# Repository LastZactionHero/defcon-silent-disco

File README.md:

# DEF CON Silent Disco Badge

A wearable silent disco. Every badge plays DJ mixes from its own memory
card to your headphones, runs a light show that matches the music, and can
**sync to a friend's badge over infrared** — same song, same moment, lights
flashing together.

## How to use it

1. Flip the **power switch**. Plug **headphones** into the top jack.
2. It starts playing where it last left off.

| Button | Does |
|---|---|
| **CHANNEL** | Next channel. Each channel is one DJ mix that loops forever. |
| **VOL + / −** | Volume, 8 steps. Hold to ramp. Bottom step is mute. |
| **SYNC** | Join a friend — see below. |
| **CHANNEL, held 10 s** | Reset the badge. |

**Syncing:** press SYNC — your music pauses and the badge listens for up to
~25 seconds. Touch your badge's jagged edge into your friend's (they
interlock — that's what the teeth are for) and it will pick up their
broadcast, jump to **their channel at their exact spot**, and both badges
shimmer to confirm. Every badge announces itself over IR every ~10 seconds,
so there's nothing to press on the other badge.

**The light show** is picked by the music: each track gets its own color
theme and animation, and every ~10 seconds the badge plays a short glitter
burst. Synced badges glitter at the same instant.

## If something's wrong

**Red blinking LEDs** are an error code — count which LEDs are lit
(leftmost = 1):

| Code | Meaning | Try |
|---|---|---|
| 1 | No SD card | Reseat the card, power cycle |
| 2 | Card is empty | Put MP3s on it (see below) |
| 3 | Card unreadable | Re-format / re-copy the card |
| 4 | Playback keeps failing | Power cycle; check the battery |

**Sounds distorted, buzzy, or "like a modem"? Swap the battery.** A dying
battery warps the audio and confuses the SD card before anything else —
it looks like a bug, and it never is.

## The SD card

Just MP3 files in the root of the card — nothing else needed:

```
/ElAndEu_Duis.mp3      ← channel 1
/InYourEyes.mp3        ← channel 2
/Sepultura.mp3         ← channel 3   (alphabetical order = channel order)
```

- Encode at **96 kbps CBR, 44.1 kHz stereo** — `firmware/tools/prepare_card.sh`
  does this for you (and matches loudness across mixes).
- The **filename chooses the light show** — rename a file, get new colors.
- A 128 MB card holds about **2 h 54 m** (~29 min × 6 channels).

## Coming soon

- **Plain MP3-player firmware** — reflash the badge as a normal
  pocket music player (next/prev/pause instead of channels + sync). The
  code exists in this repo; a one-step installer is TODO.
- A **phone app that joins the disco by camera** — the glitter bursts
  encode the channel and timecode, so a phone can watch any badge and
  start playing along. Groundwork is shipped; app is TODO.

## Flashing / updating the firmware

Everything a badge runs is in this repo — [`firmware/`](firmware/) —
including the prebuilt firmware image
[`firmware-mp3-universal.uf2`](firmware/firmware-mp3-universal.uf2)
(one image works on every badge in the run).

**The easy way** (macOS/Linux, needs Python 3 and
[`mpremote`](https://docs.micropython.org/en/latest/reference/mpremote.html)):

```sh
git clone https://github.com/LastZactionHero/defcon-silent-disco.git
cd defcon-silent-disco/firmware
tools/flash_badge.sh        # follow the prompts: plug in, wait for DONE
```

The script does the whole thing — flashes the UF2, installs the badge
software, verifies it, reboots into the disco.

**By hand:** hold **BOOTSEL** while plugging in USB → a drive called
`RPI-RP2` appears → copy the `.uf2` onto it → the badge reboots → then copy
the `.py` files from `firmware/` onto it with `mpremote`. (macOS quirk: use
the script or `dd` — a plain Finder/`cp` copy of a UF2 can silently fail.
The drive *disappearing* is how you know the flash worked.)

Full details, including rebuilding the firmware from source:
[`firmware/README.md`](firmware/README.md).

## Under the hood

RP2040 · MicroPython + native MP3 decoder · 4× addressable RGB LEDs ·
IR sync · sawtooth interlocking edges · USB-C. The full technical story —
firmware architecture, the test suite, build-your-own instructions, and
the bring-up war stories — lives in [`firmware/README.md`](firmware/README.md).
KiCad sources are in [`defcon_badge/`](defcon_badge/), fab files in
[`defcon_badge/fab_rev2.zip`](defcon_badge/fab_rev2.zip).

## Credits

Designed and built by [**Pikkolo Assembly**](https://pikkoloassembly.com/).
Demo mixes are Creative Commons (attribution in `CREDITS.txt` on each
card). MP3 decoding by the Helix decoder via
[picomp3lib](https://github.com/ikjordan/picomp3lib).

MIT licensed — see [LICENSE](LICENSE). Go make a dance floor.

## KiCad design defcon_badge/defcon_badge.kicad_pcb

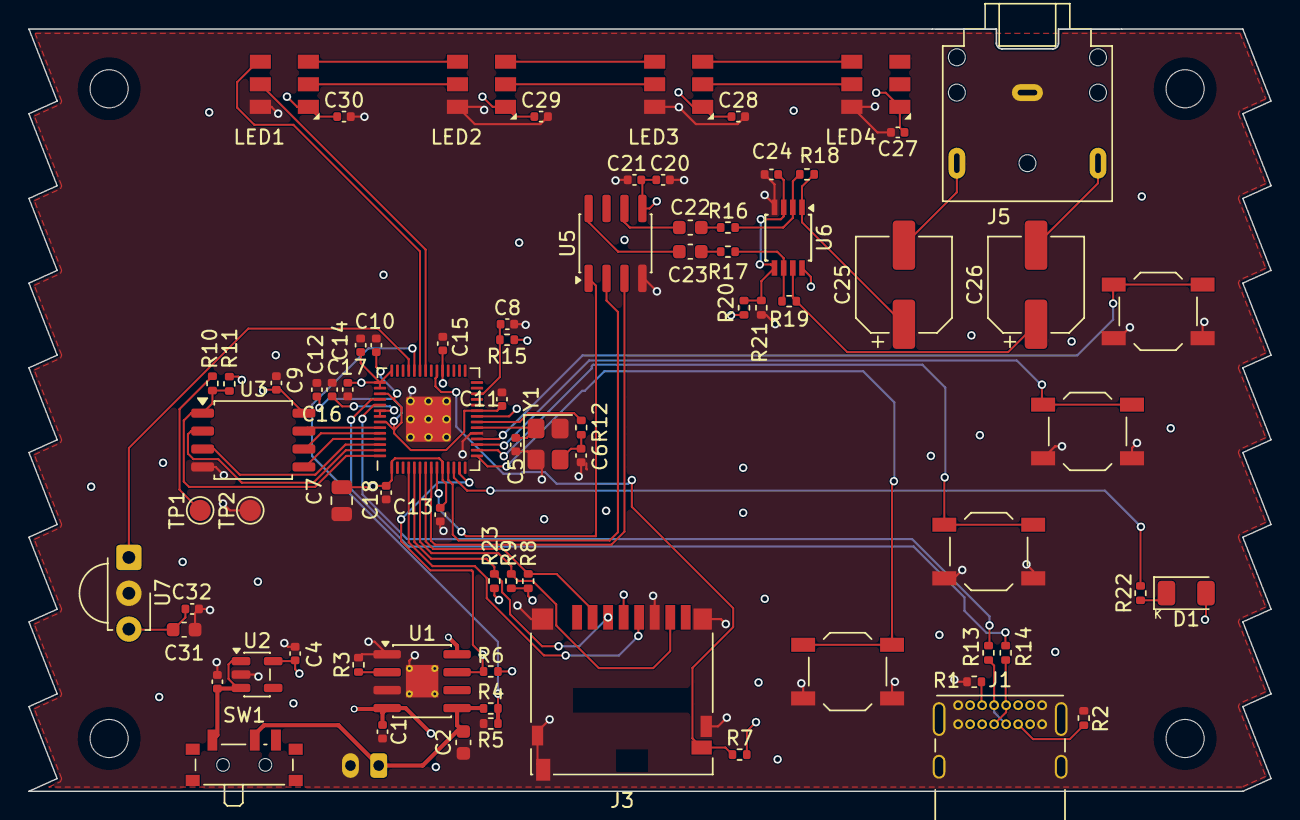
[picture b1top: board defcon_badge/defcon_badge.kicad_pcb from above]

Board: 4 copper layers, 88.0 x 54.0 mm, 82 parts (1 on the bottom side), 61 nets.

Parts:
C1, C3, C4, C12, C14: 1u; C_0402_1005Metric
C2, C22, C23, C31: 10u; C_0603_1608Metric
C5, C6: 15p; C_0402_1005Metric
C7: 1u; C_0805_2012Metric
C8: 100nF; C_0402_1005Metric
C9, C10, C11, C13, C15, C16, C17, C18, C20, C30: 100n; C_0402_1005Metric
C21, C24: 10u; C_0402_1005Metric
C25, C26: 220u; CP_Elec_6.3x5.4
C27, C28, C29, C32: 10n; C_0402_1005Metric
CHANNEL1: TS-1187A; SW_SPST_TL3342
D1: IR LED 940 nm; LED_IR_1206_3216Metric
H1, H2, H3, H4: MountingHole; MountingHole_2.7mm_M2.5
J1: USB_C_Receptacle_USB2.0_16P; USB_C_Receptacle_GCT_USB4085
J2: JST-PH 2P; JST_PH_S2B-PH-K_1x02_P2.00mm_Horizontal
J3: microSD; microSD_HC_Hirose_DM3D-SF
J5: SJ1-3523N; Jack_3.5mm_CUI_SJ1-3523N_Horizontal
LED1, LED2, LED3, LED4: SK9822; LED_SK9822_5050
R1, R2: 5.1k; R_0402_1005Metric
R3: 2.4k; R_0402_1005Metric
R4, R5, R6, R18, R19: 100k; R_0402_1005Metric
R7, R8, R9, R15, R20, R21, R23: 10k; R_0402_1005Metric
R10, R12: 1k; R_0402_1005Metric
R11: DNF; R_0402_1005Metric
R13, R14: 27; R_0402_1005Metric
R16, R17: 47k; R_0402_1005Metric
R22: 150; R_0402_1005Metric
SW1: SS-12D00; SW_SPDT_PCM12
SYNC1: TS-1187A; SW_SPST_TL3342
TP1: BOOTSEL; TestPoint_Pad_D1.5mm
TP2: GND; TestPoint_Pad_D1.5mm
U1: TP4056; HSOP-8-1EP_3.9x4.9mm_P1.27mm_EP2.3x2.3mm_ThermalVias
U2: ME6211C33M5G; SOT-23-5
U3: WM2606220057; SOIC-8_5.3x5.3mm_P1.27mm
U4: RP2040; RP2040-QFN-56
U5: TM8211; SOIC-8_3.9x4.9mm_P1.27mm
U6: TDA1308; TSSOP-8_3x3mm_P0.65mm
U7: TSOP4838; Vishay_MINICAST-3Pin
VOL+1: TS-1187A; SW_SPST_TL3342
VOL-1: TS-1187A; SW_SPST_TL3342
Y1: ABM8-272-T3; Crystal_SMD_3225-4Pin_3.2x2.5mm

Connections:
+1V1: C10.1, C11.1, C12.1, U4.23 (DVDD), U4.45 (VREG_VOUT), U4.50 (DVDD)
+3.3V: R8.1, R9.1, R23.1
+3V3: C4.1, C7.1, C9.1, C13.1, C14.1, C15.1, C16.1, C17.1, C18.1, C20.1, C21.1, C27.1, C28.1, C29.1, C30.1, C31.1, C32.1, D1.1 (K), J3.4 (VDD), LED1.4 (VDD), LED2.4 (VDD), LED3.4 (VDD), LED4.4 (VDD), R6.1, R7.2, R11.1, R15.1, R20.1, U2.5 (VOUT), U3.8 (VCC), U4.1 (IOVDD), U4.10 (IOVDD), U4.22 (IOVDD), U4.33 (IOVDD), U4.42 (IOVDD), U4.43 (ADC_AVDD), U4.44 (VREG_IN), U4.48 (USB_VDD), U4.49 (IOVDD), U5.5 (VDD), U6.8 (VCC), U7.3 (VS)
/Audio/AMP_IN1-: R16.2, R18.1, U6.2 (IN1-)
/Audio/AMP_IN2-: R17.2, R19.1, U6.6 (IN2-)
/Audio/AMP_INL: C22.2, R16.1
/Audio/AMP_INR: C23.2, R17.1
/Audio/AMP_OUTL: C25.1, R18.2, U6.1 (OUT1)
/Audio/AMP_OUTR: C26.1, R19.2, U6.7 (OUT2)
/Audio/DAC_OUTL: C22.1, U5.6 (LCH)
/Audio/DAC_OUTR: C23.1, U5.8 (RCH)
/Audio/I2S_BCK: U4.9 (GPIO7), U5.1 (BCK)
/Audio/I2S_DIN: U4.8 (GPIO6), U5.3 (DIN)
/Audio/I2S_LRCK: U4.11 (GPIO8), U5.2 (WS)
/Audio/JACK_L: C25.2, J5.T (TIP)
/Audio/JACK_R: C26.2, J5.R (RING)
/Audio/VGND: C24.1, R20.2, R21.1, U6.3 (IN1+), U6.5 (IN2+)
/IO/BTN_CH: CHANNEL1.1, U4.18 (GPIO15)
/IO/BTN_SYNC: SYNC1.1, U4.15 (GPIO12)
/IO/BTN_VOL_DN: U4.16 (GPIO13), VOL-1.1
/IO/BTN_VOL_UP: U4.17 (GPIO14), VOL+1.1
/IO/SD_CS: J3.2 (DAT3/CD), R8.2, U4.7 (GPIO5)
/IO/SD_MISO: J3.7 (DAT0), R9.2, U4.6 (GPIO4)
/IO/SD_MOSI: J3.3 (CMD), R23.2, U4.5 (GPIO3)
/IO/SD_SCK: J3.5 (CLK), U4.4 (GPIO2)
/LEDs_IR/IR_DRIVE: D1.2 (A), R22.1
/LEDs_IR/IR_RX: U4.39 (GPIO27_ADC1), U7.1 (OUT)
/LEDs_IR/IR_TX: R22.2, U4.12 (GPIO9)
/LEDs_IR/LED_DAT: LED1.1 (DIN), U4.37 (GPIO25)
/LEDs_IR/LED_SCK: LED1.2 (CIN), U4.36 (GPIO24)
/MCU_Core/BOOTSEL: R10.2, TP1.1 (1_1)
/MCU_Core/QSPI_SCLK: U3.6 (CLK), U4.52 (QSPI_SCLK)
/MCU_Core/QSPI_SD0: U3.5 (DI(IO0)), U4.53 (QSPI_SD0)
/MCU_Core/QSPI_SD1: U3.2 (DO(IO1)), U4.55 (QSPI_SD1)
/MCU_Core/QSPI_SD2: U3.3 (IO2), U4.54 (QSPI_SD2)
/MCU_Core/QSPI_SD3: U3.7 (IO3), U4.51 (QSPI_SD3)
/MCU_Core/QSPI_SS: R10.1, R11.2, U3.1 (~CS), U4.56 (QSPI_SS)
/MCU_Core/RUN: C8.1, R15.2, U4.26 (RUN)
/MCU_Core/USB_DM: J1.A7 (D-), J1.B7 (D-), R14.1
/MCU_Core/USB_DP: J1.A6 (D+), J1.B6 (D+), R13.1
/MCU_Core/VBAT_SENSE: R4.2, R5.1, U4.38 (GPIO26_ADC0)
/MCU_Core/XIN: C5.1, U4.20 (XIN), Y1.1
/MCU_Core/XOUT: R12.1, U4.21 (XOUT)
/MCU_Core/~CHRG: R6.2, U1.7 (~CHRG), U4.13 (GPIO10)
/Power/BAT: C2.1, J2.2, R4.1, SW1.2 (B), U1.5 (BAT)
/Power/BAT_SW: C3.1, SW1.1 (A), U2.1 (VIN), U2.3 (EN)
/Power/CC1: J1.A5 (CC1), R1.1
/Power/CC2: J1.B5 (CC2), R2.1
/Power/PROG_SET: R3.1, U1.2 (PROG)
/Power/VBUS: C1.1, J1.A4 (VBUS), J1.A9 (VBUS), J1.B4 (VBUS), J1.B9 (VBUS), U1.4 (VCC), U1.8 (CE)
GND: C1.2, C2.2, C3.2, C4.2, C5.2, C6.2, C7.2, C8.2, C9.2, C10.2, C11.2, C12.2, C13.2, C14.2, C15.2, C16.2, C17.2, C18.2, C20.2, C21.2, C24.2, C27.2, C28.2, C29.2, C30.2, C31.2, C32.2, CHANNEL1.2, J1.A1 (GND), J1.A12 (GND), J1.B1 (GND), J1.B12 (GND), J1.SH (SHIELD), J2.1, J3.6 (VSS), J3.10 (DET_A), J3.SH (SHIELD), J5.S (SLEEVE), LED1.3 (GND), LED2.3 (GND), LED3.3 (GND), LED4.3 (GND), R1.2, R2.2, R3.2, R5.2, R21.2, SYNC1.2, TP2.1 (1_1), U1.1 (TEMP), U1.3 (GND), U1.9 (EP), U2.2 (GND), U3.4 (GND), U4.19 (TESTEN), U4.57 (GND), U5.4 (GND), U6.4 (VEE), U7.2 (GND), VOL+1.2, VOL-1.2, Y1.2, Y1.4
unnamed: C6.1, R12.2, Y1.3
unnamed: LED1.5 (COUT), LED2.2 (CIN)
unnamed: LED1.6 (DOUT), LED2.1 (DIN)
unnamed: LED2.5 (COUT), LED3.2 (CIN)
unnamed: LED2.6 (DOUT), LED3.1 (DIN)
unnamed: LED3.5 (COUT), LED4.2 (CIN)
unnamed: LED3.6 (DOUT), LED4.1 (DIN)
unnamed: R14.2, U4.46 (USB_DM)
unnamed: R13.2, U4.47 (USB_DP)
SD_CD: J3.9 (DET_B), R7.1, U4.34 (GPIO22)

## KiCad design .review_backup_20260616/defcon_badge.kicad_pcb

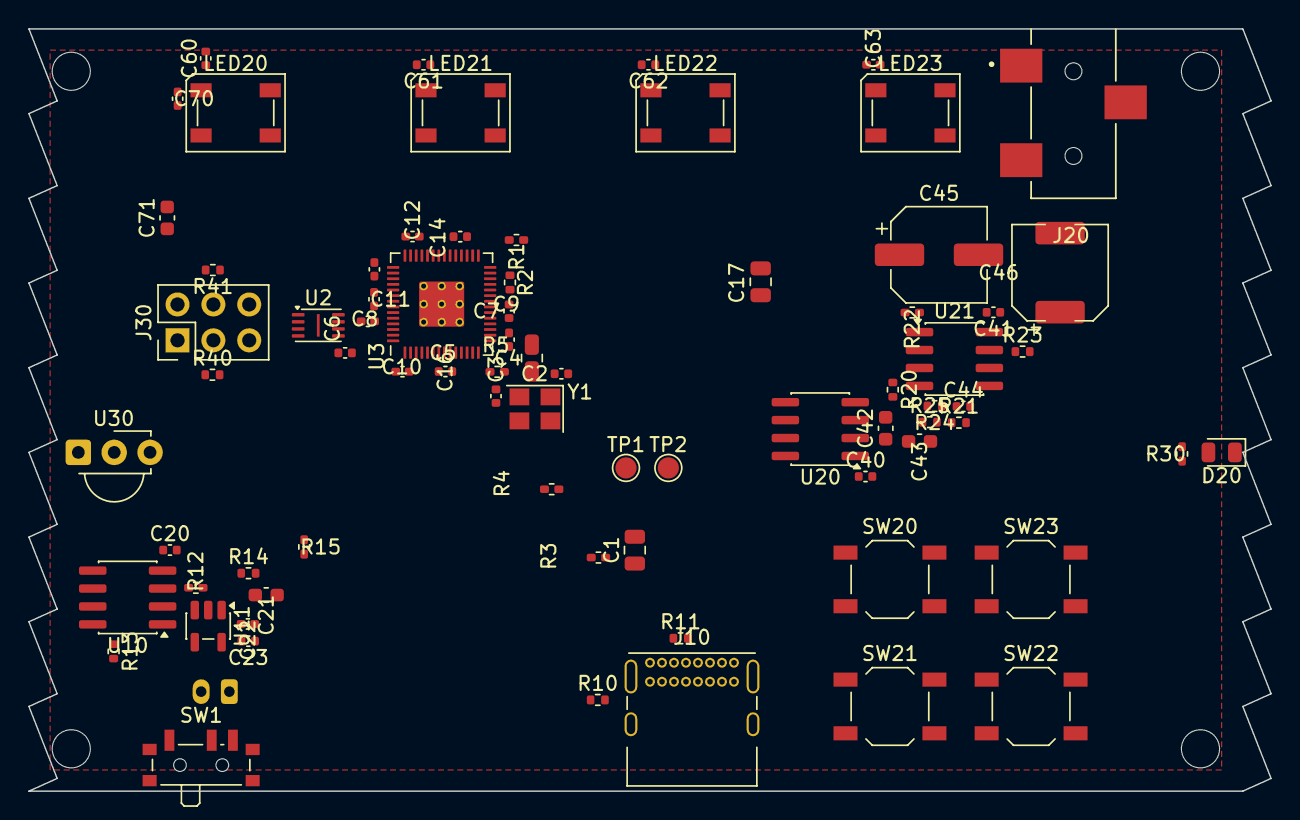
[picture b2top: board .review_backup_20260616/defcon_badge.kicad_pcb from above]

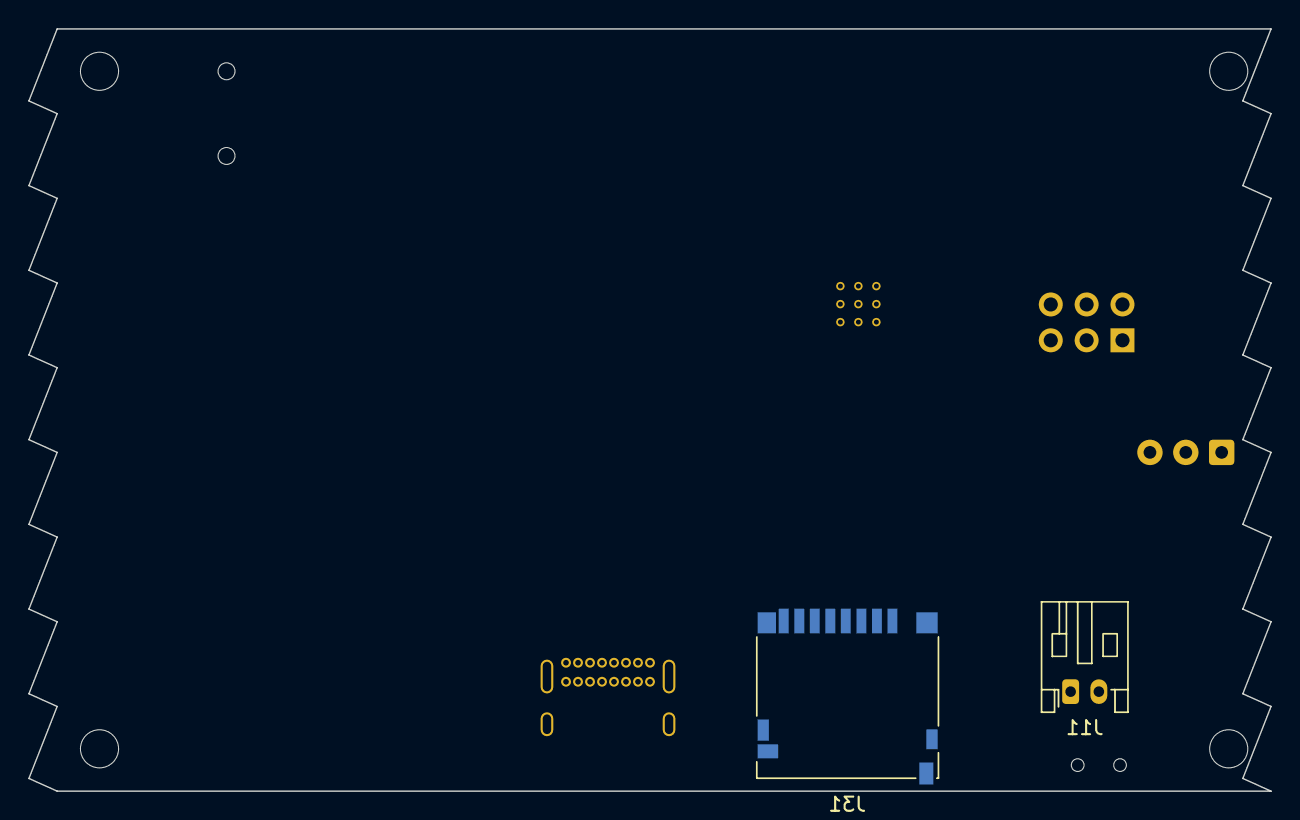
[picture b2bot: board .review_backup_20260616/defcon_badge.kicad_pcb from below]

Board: 4 copper layers, 88.0 x 54.0 mm, 81 parts (2 on the bottom side), 59 nets, no tracks yet.

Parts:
C1, C4, C17: 10u; C_0805_2012Metric
C2, C3: 15p; C_0402_1005Metric
C5, C6, C7, C9, C11, C12, C14, C16, C40, C70: 100n; C_0402_1005Metric
C8, C10, C20, C22, C23: 1u; C_0402_1005Metric
C21, C42, C43, C71: 10u; C_0603_1608Metric
C41, C44: 10u; C_0402_1005Metric
C45, C46: 220u; CP_Elec_6.3x5.4
C60, C61, C62, C63: 10n; C_0402_1005Metric
D20: IR LED 940 nm; LED_0805_2012Metric
H1, H2, H3, H4: MountingHole; MountingHole_2.7mm_M2.5
J10: USB_C_Receptacle_GCT_USB4085
J11: JST-PH 2P; JST_PH_S2B-PH-K_1x02_P2.00mm_Horizontal
J20: AMPHENOL_10038075-D0P
J30: SAO 2x3; PinHeader_2x03_P2.54mm_Vertical
J31: microSD; microSD_HC_Hirose_DM3D-SF
LED20, LED21, LED22, LED23: SK9822-EC20; LED_SK6812_PLCC4_5.0x5.0mm_P3.2mm
R1, R5: 1k; R_0402_1005Metric
R2: DNF; R_0402_1005Metric
R3, R4: 27; R_0402_1005Metric
R10, R11: 5.1k; R_0402_1005Metric
R12: 2.4k; R_0402_1005Metric
R13, R14, R15, R22, R23: 100k; R_0402_1005Metric
R20, R21: 47k; R_0402_1005Metric
R24, R25: 10k; R_0402_1005Metric
R30: 68; R_0402_1005Metric
R40, R41: 4.7k; R_0402_1005Metric
SW1: SS-12D00; SW_SPDT_PCM12
SW20, SW21, SW22, SW23: TS-1187A; SW_SPST_TL3342
TP1, TP2: TestPoint_Pad_D1.5mm
U2: W25Q16JVUXIQ; Winbond_USON-8-1EP_3x2mm_P0.5mm_EP0.2x1.6mm
U3: RP2040; RP2040-QFN-56
U10: TP4056; SOIC-8_3.9x4.9mm_P1.27mm
U11: ME6211C33M5G; SOT-23-5
U20: TM8211; SOIC-8_3.9x4.9mm_P1.27mm
U21: TDA1308; SOIC-8_3.9x4.9mm_P1.27mm
U30: TSOP4838; Vishay_MINICAST-3Pin
Y1: ABM8-272-T3; Crystal_SMD_3225-4Pin_3.2x2.5mm

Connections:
+1V1: C6.1, C7.1, C8.1, U3.23 (DVDD), U3.45 (VREG_VOUT), U3.50 (DVDD)
+3V3: C4.1, C5.1, C9.1, C10.1, C11.1, C12.1, C14.1, C16.1, R2.1, U2.8 (VCC), U3.1 (IOVDD), U3.10 (IOVDD), U3.22 (IOVDD), U3.33 (IOVDD), U3.42 (IOVDD), U3.43 (ADC_AVDD), U3.44 (VREG_IN), U3.48 (USB_VDD), U3.49 (IOVDD)
/Audio/+3V3: C40.1, C41.1, R24.1, U20.1 (VDD), U21.8 (VCC)
/Audio/AMP_IN1-: R20.2, R22.1, U21.2 (IN1-)
/Audio/AMP_IN2-: R21.2, R23.1, U21.6 (IN2-)
/Audio/AMP_INL: C42.2, R20.1
/Audio/AMP_INR: C43.2, R21.1
/Audio/AMP_OUTL: C45.1, R22.2, U21.1 (OUT1)
/Audio/AMP_OUTR: C46.1, R23.2, U21.7 (OUT2)
/Audio/DAC_OUTL: C42.1, U20.2 (VLL)
/Audio/DAC_OUTR: C43.1, U20.3 (VRR)
/Audio/I2S_BCK: U3.9 (GPIO7), U20.6 (BCK)
/Audio/I2S_DIN: U3.8 (GPIO6), U20.7 (DIN)
/Audio/I2S_LRCK: U3.11 (GPIO8), U20.5 (WS)
/Audio/JACK_L: C45.2, J20.3
/Audio/JACK_R: C46.2, J20.1
/Audio/VGND: C44.1, R24.2, R25.1, U21.3 (IN1+), U21.5 (IN2+)
/IO/+3V3: J30.2, J31.4 (VDD), R40.1, R41.1
/IO/BTN_CH: SW20.1, U3.15 (GPIO12)
/IO/BTN_VOL_DN: SW22.1, U3.17 (GPIO14)
/IO/BTN_VOL_UP: SW21.1, U3.16 (GPIO13)
/IO/SAO_GPIO1: J30.5, U3.31 (GPIO20)
/IO/SAO_GPIO2: J30.6, U3.32 (GPIO21)
/IO/SAO_SCL: J30.4, R41.2, U3.28 (GPIO17)
/IO/SAO_SDA: J30.3, R40.2, U3.27 (GPIO16)
/IO/SD_CS: J31.2 (DAT3/CD), U3.7 (GPIO5)
/IO/SD_MISO: J31.7 (DAT0), U3.6 (GPIO4)
/IO/SD_MOSI: J31.3 (CMD), U3.5 (GPIO3)
/IO/SD_SCK: J31.5 (CLK), U3.4 (GPIO2)
/LEDs_IR/+3V3: C60.1, C61.1, C62.1, C63.1, C70.1, C71.1, D20.2 (A), LED20.1 (VDD), LED21.1 (VDD), LED22.1 (VDD), LED23.1 (VDD), U30.3 (VS)
/LEDs_IR/IR_DRIVE: D20.1 (K), R30.1
/LEDs_IR/IR_RX: U3.18 (GPIO15), U30.1 (OUT)
/LEDs_IR/IR_TX: R30.2, U3.12 (GPIO9)
/LEDs_IR/LED_DAT: LED20.2 (DIN), U3.14 (GPIO11)
/LEDs_IR/LED_SCK: LED20.3 (CIN), U3.13 (GPIO10)
/MCU_Core/QSPI_SCLK: U2.6 (CLK), U3.52 (QSPI_SCLK)
/MCU_Core/QSPI_SD0: U2.5 (DI(IO0)), U3.53 (QSPI_SD0)
/MCU_Core/QSPI_SD1: U2.2 (DO(IO1)), U3.55 (QSPI_SD1)
/MCU_Core/QSPI_SD2: U2.3 (IO2), U3.54 (QSPI_SD2)
/MCU_Core/QSPI_SD3: U2.7 (IO3), U3.51 (QSPI_SD3)
/MCU_Core/QSPI_SS: R1.1, R2.2, U2.1 (~CS), U3.56 (QSPI_SS)
/MCU_Core/VBAT_SENSE: R14.2, R15.1, U3.38 (GPIO26_ADC0)
/MCU_Core/XIN: C2.1, U3.20 (XIN), Y1.1
/MCU_Core/XOUT: R5.1, U3.21 (XOUT)
/MCU_Core/~CHRG: R13.2, U3.29 (GPIO18), U10.7 (~CHRG)
/Power/+3V3: C23.1, R13.1, U10.8 (CE), U11.5 (VOUT)
/Power/BAT: C21.1, J11.1, R14.1, SW1.2 (B), U10.5 (BAT)
/Power/BAT_SW: C22.1, SW1.1 (A), U11.1 (VIN), U11.3 (EN)
/Power/CC2: J10.A5, J10.B5, R11.1
/Power/PROG_SET: R12.1, U10.2 (PROG)
/Power/VBUS: C20.1, J10.A4, J10.A9, J10.B4, J10.B9, U10.4 (VCC)
BOOTSEL: R1.2, TP1.1
GND: C1.2, C2.2, C3.2, C4.2, C5.2, C6.2, C7.2, C8.2, C9.2, C10.2, C11.2, C12.2, C14.2, C16.2, C20.2, C21.2, C22.2, C23.2, C40.2, C41.2, C44.2, C60.2, C61.2, C62.2, C63.2, C70.2, C71.2, J10.A1, J10.A12, J10.B1, J10.B12, J10.SH, J11.2, J20.2, J30.1, J31.6 (VSS), J31.SH (SHIELD), R10.1, R10.2, R11.2, R12.2, R15.2, R25.2, SW20.2, SW21.2, SW22.2, SW23.2, TP2.1, U2.4 (GND), U3.19 (TESTEN), U3.57 (GND), U10.1 (TEMP), U10.3 (GND), U11.2 (GND), U20.4 (VSS), U21.4 (VEE), U30.2 (GND), Y1.2, Y1.4
unnamed: C3.1, R5.2, Y1.3
unnamed: LED20.4 (DOUT), LED21.2 (DIN)
unnamed: LED21.4 (DOUT), LED22.2 (DIN)
unnamed: LED22.4 (DOUT), LED23.2 (DIN)
unnamed: J10.A7, J10.B7, R4.2, U3.46 (USB_DM)
unnamed: J10.A6, J10.B6, R3.2, U3.47 (USB_DP)

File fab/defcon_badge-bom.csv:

"Reference","Value","Footprint","MPN","LCSC"
"C1,C4,C17","10u","Capacitor_SMD:C_0805_2012Metric","",""
"C2,C3","15p","Capacitor_SMD:C_0402_1005Metric","",""
"C5-C7,C9,C11,C12,C14,C16,C40,C70","100n","Capacitor_SMD:C_0402_1005Metric","CL05B104KO5NNNC","C1525"
"C8,C10,C20,C22,C23","1u","Capacitor_SMD:C_0402_1005Metric","CL05A105KP5NNNC","C52923"
"C21,C42,C43,C71","10u","Capacitor_SMD:C_0603_1608Metric","CL10A106KP8NNNC","C19702"
"C41,C44","10u","Capacitor_SMD:C_0402_1005Metric","",""
"C45,C46","220u","Capacitor_SMD:CP_Elec_6.3x5.4","",""
"C60-C63","10n","Capacitor_SMD:C_0402_1005Metric","CL05B103KB5NNNC","C57112"
"D20","IR LED 940 nm","LED_SMD:LED_0805_2012Metric","IR15-21C/TR8","C72037"
"H1-H4","MountingHole","MountingHole:MountingHole_2.7mm_M2.5","",""
"J10","USB_C_Receptacle_USB2.0_16P","Connector_USB:USB_C_Receptacle_GCT_USB4085","USB4085","C404969"
"J11","JST-PH 2P","Connector_JST:JST_PH_S2B-PH-K_1x02_P2.00mm_Horizontal","S2B-PH-K-S","C131350"
"J20","PJ-320A","Connector_Audio:Jack_3.5mm_QingPu_WQP-PJ398SM_Vertical_CircularHoles","PJ-320A","C720466"
"J30","SAO 2x3","Connector_PinHeader_2.54mm:PinHeader_2x03_P2.54mm_Vertical","PRPC003DAAN-RC","C124378"
"J31","microSD","Connector_Card:microSD_HC_Hirose_DM3D-SF","TF-PUSH-A","C146885"
"J32","UART debug","Connector_PinHeader_2.54mm:PinHeader_1x03_P2.54mm_Vertical","",""
"J33","Dev/SWD header","Connector_PinHeader_2.54mm:PinHeader_1x05_P2.54mm_Vertical","",""
"LED20-LED23","SK9822-EC20","LED_SMD:LED_SK6812_PLCC4_5.0x5.0mm_P3.2mm","SK9822-EC20","C2890389"
"R1,R5","1k","Resistor_SMD:R_0402_1005Metric","",""
"R2","DNF","Resistor_SMD:R_0402_1005Metric","",""
"R3,R4","27","Resistor_SMD:R_0402_1005Metric","",""
"R10,R11","5.1k","Resistor_SMD:R_0402_1005Metric","RC0402FR-075K1L","C23186"
"R12","2.4k","Resistor_SMD:R_0402_1005Metric","RC0402FR-072K4L","C25789"
"R13-R15,R22,R23","100k","Resistor_SMD:R_0402_1005Metric","RC0402FR-07100KL","C25741"
"R20,R21","47k","Resistor_SMD:R_0402_1005Metric","RC0402FR-0747KL","C25819"
"R24,R25","10k","Resistor_SMD:R_0402_1005Metric","RC0402FR-0710KL","C25744"
"R30","150","Resistor_SMD:R_0402_1005Metric","",""
"R40,R41","4.7k","Resistor_SMD:R_0402_1005Metric","RC0402FR-074K7L","C25900"
"SW1","SS-12D00","Button_Switch_SMD:SW_SPDT_PCM12","MSK-12C02","C431540"
"SW20-SW22","TS-1187A","Button_Switch_SMD:SW_SPST_TL3342","TS-1187A-B-A-B","C455257"
"U2","W25Q16JVUXIQ","Package_SON:Winbond_USON-8-1EP_3x2mm_P0.5mm_EP0.2x1.6mm","",""
"U3","RP2040","RP2040_minimal:RP2040-QFN-56","",""
"U10","TP4056","Package_SO:SOIC-8_3.9x4.9mm_P1.27mm","TP4056","C16581"
"U11","ME6211C33M5G","Package_TO_SOT_SMD:SOT-23-5","ME6211C33M5G","C82942"
"U20","TM8211","Package_SO:SOIC-8_3.9x4.9mm_P1.27mm","TM8211","C82978"
"U21","TDA1308","Package_SO:SOIC-8_3.9x4.9mm_P1.27mm","TDA1308AT","C8434"
"U30","TSOP4838","OptoDevice:Vishay_MINICAST-3Pin","TSOP4838","C90701"
"Y1","ABM8-272-T3","Crystal:Crystal_SMD_3225-4Pin_3.2x2.5mm","",""

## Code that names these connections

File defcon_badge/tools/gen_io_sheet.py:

#!/usr/bin/env python3
"""Generate IO.kicad_sch — 4× tactile + SAO 2×3 + microSD."""
import sys
from pathlib import Path
sys.path.insert(0, str(Path(__file__).parent))
from kicad_sheet_gen import SheetGen, CustomPin


def build() -> SheetGen:
    sg = SheetGen(
        name="IO",
        title="DEFCON Silent Disco Badge — IO",
        file_uuid="2b85d325-facd-43cf-ba3c-e148f65c3ed6",
        sheet_symbol_uuid="608539de-722a-4bca-b1da-2c313b60cd6f",
        page="6",
        paper="A3",
        comments=[
            "3× TS-1187A tactile (CH / VOL+ / VOL−) via internal RP2040 pullups",
            "Standard SAO v1.69 2×3 (3V3 / GND / SDA / SCL / GP1 / GP2), 4.7k SAO_SDA/SCL pullups",
            "microSD push socket on SPI0",
        ],
    )

    for lib, sym in [
        ("Device.kicad_sym", "R"),
        ("Switch.kicad_sym", "SW_Push"),
        ("Connector.kicad_sym", "Micro_SD_Card_Det2"),
        ("Connector_Generic.kicad_sym", "Conn_02x03_Odd_Even"),
        ("Connector_Generic.kicad_sym", "Conn_01x03"),
        ("power.kicad_sym", "+3V3"),
        ("power.kicad_sym", "GND"),
    ]:
        sg.add_stock(lib, sym)

    sg.add_text(
        "IO — badge_hw_design.md §Buttons, §SAO, §Connectors.\\n"
        "Buttons → GND with RP2040 internal pullups. SAO 2×3 standard pinout.\\n"
        "microSD on SPI0 (SCK=GP2, MOSI=GP3, MISO=GP4, CS=GP5).\\n"
        "4.7k I2C pullups for SAO bus (RP2040 internal pulls are too weak).",
        25, 25,
    )

    # ----- Four tactile buttons (CH / VOL+ / VOL- / SYNC) -----
    sg.place("Switch:SW_Push", "SW20", "TS-1187A",
             "Button_Switch_SMD:SW_SPST_TL3342", 50, 60,
             mpn="TS-1187A-B-A-B", lcsc="C455257",
             desc="Channel button (CH), 6mm tactile")
    sg.place("Switch:SW_Push", "SW21", "TS-1187A",
             "Button_Switch_SMD:SW_SPST_TL3342", 70, 60,
             mpn="TS-1187A-B-A-B", lcsc="C455257",
             desc="Volume up")
    sg.place("Switch:SW_Push", "SW22", "TS-1187A",
             "Button_Switch_SMD:SW_SPST_TL3342", 90, 60,
             mpn="TS-1187A-B-A-B", lcsc="C455257",
             desc="Volume down")
    sg.place("Switch:SW_Push", "SW23", "TS-1187A",
             "Button_Switch_SMD:SW_SPST_TL3342", 110, 60,
             mpn="TS-1187A-B-A-B", lcsc="C455257",
             desc="Sync (tap-to-sync) button")

    sg.label_at_pin("SW20", "1", "BTN_CH")
    sg.power_at_pin("SW20", "2", "GND", pwr_ref="#PWR_SW20")
    sg.label_at_pin("SW21", "1", "BTN_VOL_UP")
    sg.power_at_pin("SW21", "2", "GND", pwr_ref="#PWR_SW21")
    sg.label_at_pin("SW22", "1", "BTN_VOL_DN")
    sg.power_at_pin("SW22", "2", "GND", pwr_ref="#PWR_SW22")
    sg.label_at_pin("SW23", "1", "BTN_SYNC")
    sg.power_at_pin("SW23", "2", "GND", pwr_ref="#PWR_SW23")

    # ----- SAO 2×3 header -----
    # Standard SAO v1.69bis pinout (official badge.team / Hackaday spec):
    #   1: +3V3, 2: GND, 3: SDA, 4: SCL, 5: GPIO1, 6: GPIO2
    # (pin1=VCC, pin2=GND — NOT the reverse; a swapped pair reverse-powers any
    #  standards-compliant SAO add-on.)
    sg.place("Connector_Generic:Conn_02x03_Odd_Even", "J30", "SAO 2x3",
             "Connector_PinHeader_2.54mm:PinHeader_2x03_P2.54mm_Vertical", 130, 70,
             mpn="PRPC003DAAN-RC", lcsc="C124378",
             desc="SAO v1.69 2x3 header — DEFCON shitty add-on")
    sg.label_at_pin("J30", "1", "+3V3")
    sg.power_at_pin("J30", "2", "GND", pwr_ref="#PWR_J30_1")
    sg.label_at_pin("J30", "3", "SAO_SDA")
    sg.label_at_pin("J30", "4", "SAO_SCL")
    sg.label_at_pin("J30", "5", "SAO_GPIO1")
    sg.label_at_pin("J30", "6", "SAO_GPIO2")

    # SAO I2C pullups (4.7k each on SDA, SCL, to +3V3)
    sg.place("Device:R", "R40", "4.7k", "Resistor_SMD:R_0402_1005Metric",
             160, 60, desc="SAO_SDA pullup")
    sg.place("Device:R", "R41", "4.7k", "Resistor_SMD:R_0402_1005Metric",
             170, 60, desc="SAO_SCL pullup")
    sg.label_at_pin("R40", "1", "+3V3")
    sg.label_at_pin("R40", "2", "SAO_SDA")
    sg.label_at_pin("R41", "1", "+3V3")
    sg.label_at_pin("R41", "2", "SAO_SCL")

    # ----- microSD card socket -----
    # Det2 symbol exposes BOTH card-detect switch terminals (pin 9 DET_B, pin 10
    # DET_A). The DM3D-SF detect switch sits between 9 and 10 — pin 10 MUST go to
    # GND so a card closing the switch pulls the pulled-up SD_CD (pin 9) low.
    # (Det1 has no pin 10, which left the switch's far side floating = dead CD.)
    sg.place("Connector:Micro_SD_Card_Det2", "J31", "microSD",
             "Connector_Card:microSD_HC_Hirose_DM3D-SF", 80, 130,
             mpn="TF-PUSH-A", lcsc="C146885",
             desc="microSD push socket, hinged tray")
    # SPI mode wiring:
    #   pin 1: DAT2/RSV (no_connect)
    #   pin 2: CD/DAT3 = CS
    #   pin 3: CMD = MOSI
    #   pin 4: VDD
    #   pin 5: CLK = SCK
    #   pin 6: VSS = GND
    #   pin 7: DAT0 = MISO
    #   pin 8: DAT1/RSV (no_connect)
    #   pin 9: CD (card detect, optional)
    #   SH: shield → GND
    sg.nc_at_pin("J31", "1")     # DAT2 / RSV
    sg.label_at_pin("J31", "2", "SD_CS")
    sg.label_at_pin("J31", "3", "SD_MOSI")
    sg.label_at_pin("J31", "4", "+3V3")
    sg.label_at_pin("J31", "5", "SD_SCK")
    sg.power_at_pin("J31", "6", "GND", pwr_ref="#PWR_J31_6")
    sg.label_at_pin("J31", "7", "SD_MISO")
    sg.nc_at_pin("J31", "8")     # DAT1 / RSV
    sg.global_label_at_pin("J31", "9", "SD_CD")  # DET_B: CD switch -> spare GPIO via global net
    sg.power_at_pin("J31", "10", "GND", pwr_ref="#PWR_J31_10")  # DET_A: switch other terminal -> GND
    sg.power_at_pin("J31", "SH", "GND", pwr_ref="#PWR_J31_SH")
    # Card-detect pull-up: the DET switch shorts pin 9 to the grounded shield when a
    # card is inserted, so SD_CD reads LOW = card present; R42 holds it high when empty.
    sg.place("Device:R", "R42", "10k", "Resistor_SMD:R_0402_1005Metric", 110, 110,
             desc="microSD card-detect pull-up to +3V3")
    sg.global_label_at_pin("R42", "1", "SD_CD")
    sg.label_at_pin("R42", "2", "+3V3")

    # (Debug UART header J32 removed — not used; programming is via BOOTSEL/USB.)

    # ----- Cross-sheet hier_labels -----
    sg.add_hier("SD_SCK",     35, 55, shape="input",         rot=0)
    sg.add_hier("SD_MOSI",    35, 65, shape="input",         rot=0)
    sg.add_hier("SD_MISO",    35, 75, shape="output",        rot=0)
    sg.add_hier("SD_CS",      35, 85, shape="input",         rot=0)
    sg.add_hier("BTN_CH",     35, 100, shape="output",       rot=0)
    sg.add_hier("BTN_VOL_UP", 35, 110, shape="output",       rot=0)
    sg.add_hier("BTN_VOL_DN", 35, 120, shape="output",       rot=0)
    sg.add_hier("BTN_SYNC",   35, 130, shape="output",       rot=0)
    sg.add_hier("SAO_SDA",    35, 135, shape="bidirectional", rot=0)
    sg.add_hier("SAO_SCL",    35, 145, shape="input",        rot=0)
    sg.add_hier("SAO_GPIO1",  35, 155, shape="bidirectional", rot=0)
    sg.add_hier("SAO_GPIO2",  35, 165, shape="bidirectional", rot=0)

    return sg


if __name__ == "__main__":
    sg = build()
    out = Path(__file__).parent.parent / "IO.kicad_sch"
    out.write_text(sg.render())
    print(f"wrote {out}")

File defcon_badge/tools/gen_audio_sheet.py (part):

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    sg.power_at_pin("C41", "2", "GND", pwr_ref="#PWR_C41")

    # I2S in from hier_labels (added below). Pin order: BCK, LRCK(WS), DIN
    sg.label_at_pin("U20", "1", "I2S_BCK")       # BCK = pin 1
    sg.label_at_pin("U20", "2", "I2S_LRCK")      # WS  = pin 2
    sg.label_at_pin("U20", "3", "I2S_DIN")       # DIN = pin 3
    sg.nc_at_pin("U20", "7")  # TM8211 pin 7 NC

    # DAC outputs → coupling caps → amp inputs (LCH=pin6, RCH=pin8 per PT8211)
    sg.label_at_pin("U20", "6", "DAC_OUTL")      # LCH = pin 6
    sg.label_at_pin("U20", "8", "DAC_OUTR")      # RCH = pin 8

    # 10 µF DAC→amp coupling (vertical caps, spaced apart so stub labels don't collide)
    sg.place("Device:C", "C42", "10u", "Capacitor_SMD:C_0603_1608Metric", 100, 65,
             desc="L channel DAC→amp coupling")
    sg.place("Device:C", "C43", "10u", "Capacitor_SMD:C_0603_1608Metric", 100, 95,
             desc="R channel DAC→amp coupling")
    sg.label_at_pin("C42", "1", "DAC_OUTL")
    sg.label_at_pin("C42", "2", "AMP_INL")
    sg.label_at_pin("C43", "1", "DAC_OUTR")
    sg.label_at_pin("C43", "2", "AMP_INR")

    # ----- Amp section -----
    sg.place("badge:TDA1308", "U21", "TDA1308",
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             desc="L amp input")
    sg.place("Device:R", "R21", "47k", "Resistor_SMD:R_0402_1005Metric", 120, 95,
             desc="R amp input")
    sg.label_at_pin("R20", "1", "AMP_INL")
    sg.label_at_pin("R20", "2", "AMP_IN1-")
    sg.label_at_pin("R21", "1", "AMP_INR")
    sg.label_at_pin("R21", "2", "AMP_IN2-")
    # connect inverting inputs of each opamp half
    sg.label_at_pin("U21", "2", "AMP_IN1-")
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    sg.place("Device:R", "R23", "100k", "Resistor_SMD:R_0402_1005Metric", 145, 95,
             desc="R feedback")
    sg.label_at_pin("R22", "1", "AMP_IN1-")
    sg.label_at_pin("R22", "2", "AMP_OUTL")
    sg.label_at_pin("R23", "1", "AMP_IN2-")
    sg.label_at_pin("R23", "2", "AMP_OUTR")

    # Amp outputs
    sg.label_at_pin("U21", "1", "AMP_OUTL")
    sg.label_at_pin("U21", "7", "AMP_OUTR")

    # Virtual ground (non-inverting inputs)
    # 10k/10k divider + 10µF cap
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    sg.place("Device:C", "C44", "10u", "Capacitor_SMD:C_0402_1005Metric", 175, 113,
             desc="VGND bypass")
    sg.label_at_pin("R24", "1", "+3V3")
    sg.label_at_pin("R24", "2", "VGND")
    sg.label_at_pin("R25", "1", "VGND")
    sg.power_at_pin("R25", "2", "GND", pwr_ref="#PWR_R25")
    sg.label_at_pin("C44", "1", "VGND")
    sg.power_at_pin("C44", "2", "GND", pwr_ref="#PWR_C44")
    # IN+ inputs to VGND
    sg.label_at_pin("U21", "3", "VGND")  # IN1+
    sg.label_at_pin("U21", "5", "VGND")  # IN2+

    # 220µF output coupling caps (electrolytic — use CP polarized symbol)
    sg.place("Device:C_Polarized", "C45", "220u",
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    sg.place("Device:C_Polarized", "C46", "220u",
             "Capacitor_SMD:CP_Elec_6.3x5.4", 180, 90,
             desc="R output coupling (electrolytic, 6.3V)")
    sg.label_at_pin("C45", "1", "AMP_OUTL")
    sg.label_at_pin("C45", "2", "JACK_L")
    sg.label_at_pin("C46", "1", "AMP_OUTR")
    sg.label_at_pin("C46", "2", "JACK_R")

    # ----- Jack -----
    # CUI SJ1-3523N: 3.5mm stereo TRS, through-hole, horizontal/edge-mount.
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             "Connector_Audio:Jack_3.5mm_CUI_SJ1-3523N_Horizontal",
             215, 80, mpn="SJ1-3523N",
             desc="3.5mm stereo TRS jack (CUI SJ1-3523N), edge-mount")
    sg.label_at_pin("J20", "T", "JACK_L")
    sg.label_at_pin("J20", "R", "JACK_R")
    sg.power_at_pin("J20", "S", "GND", pwr_ref="#PWR_J20")
    sg.nc_at_pin("J20", "R2")  # mic ring — TRS-only use, not on this footprint
    sg.nc_at_pin("J20", "D")   # sleeve-detect — not on this footprint
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
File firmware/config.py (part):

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# All four LEDs must share the same physical orientation or the chain breaks.
# GP24/GP25 are NOT hardware-SPI capable on RP2040 -> the driver bit-bangs.
LED_CLK = 24
LED_DAT = 25
LED_COUNT = 4

# Master LED kill switch, for isolating audio noise.
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#   VOL-    GP13  -> "vol_down"
#   VOL+    GP14  -> "vol_up"
#   CH      GP15  -> "play_pause" (CH button repurposed)
BTN_SYNC = 12
BTN_VOL_DN = 13
BTN_VOL_UP = 14
BTN_PLAY = 15

# ---------------------------------------------------------------------------
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# board, so keep the clock conservative.  Measured read throughput ~45-51 KB/s
# at 1 MHz -> pick audio formats that fit (see BADGE.md / tools/prepare_card.sh).
SD_SPI_ID = 0
SD_SCK = 2
SD_MOSI = 3
SD_MISO = 4
SD_CS = 5
SD_BAUD_INIT = 400_000     # low speed for card init
# Data phase: 4 MHz verified byte-perfect on this board (512 KB sha256-matched
# host copy at 188.7 KB/s, 2026-07-01) despite the missing MISO pull-up.
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# ---------------------------------------------------------------------------
# TX: IR LED driven active-LOW through a resistor; modulate a 38 kHz carrier.
# RX: TSOP4838 demodulator, output active-LOW (idles high, low = carrier seen).
IR_TX = 9
IR_RX = 27

# ---------------------------------------------------------------------------
# Battery sense (OPTIONAL -- requires a 2-resistor bodge)
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
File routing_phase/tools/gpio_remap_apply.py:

#!/usr/bin/env python3
"""gpio_remap_apply.py — apply the R2 GPIO remap by permuting U3-pin LOCAL LABELS in MCU_Core.

The remap moves 6 nets to destination-facing RP2040 pins by relabeling (the only semantically-correct
remap on a function-named symbol — the silicon pin keeps its identity, the NET moves). Because the
displaced pads are unused-GPIO no-connects, the whole thing is a PERMUTATION of the same 11 local-label
strings across 11 pin positions: no net is created or destroyed, just repositioned. That property is
the safety guarantee — verified before and after.

Each label is matched by (old_text + exact (at x y) position) so the edit is unambiguous. The tool
asserts every label currently reads its expected old text before touching anything; any mismatch aborts.

Usage: gpio_remap_apply.py <sheet.kicad_sch>     (edits in place; run on a /tmp copy first)
Prints the 11 swaps. The matching PCB pad-net permutation is applied separately (pcb_runner).
"""
from __future__ import annotations
import re, sys
from pathlib import Path

# pad -> (label x, label y, OLD text, NEW text). y from sch_pin_resolver (/tmp/pin_labels.json).
PERM = [
    (13, 245.11, 137.16, "LED_SCK",     "~{CHRG}"),
    (14, 245.11, 139.70, "LED_DAT",     "GPIO24"),
    (18, 245.11, 149.86, "IR_RX",       "GPIO25"),
    (27, 245.11, 152.40, "SAO_SDA",     "GPIO27_ADC1"),
    (28, 245.11, 154.94, "SAO_SCL",     "GPIO28_ADC2"),
    (29, 245.11, 157.48, "~{CHRG}",     "GPIO29_ADC3"),
    (36, 245.11, 172.72, "GPIO24",      "LED_SCK"),
    (37, 245.11, 175.26, "GPIO25",      "LED_DAT"),
    (39, 245.11, 182.88, "GPIO27_ADC1", "IR_RX"),
    (40, 245.11, 185.42, "GPIO28_ADC2", "SAO_SDA"),
    (41, 245.11, 187.96, "GPIO29_ADC3", "SAO_SCL"),
]

def fnum(v):  # format like KiCad (137.16 not 137.160; 139.7 not 139.70)
    return ("%f" % v).rstrip("0").rstrip(".")

def main():
    sheet = Path(sys.argv[1])
    txt = sheet.read_text()
    # permutation sanity: same multiset of strings in and out
    assert sorted(o for *_, o, _ in PERM) == sorted(n for *_, n in PERM), "NOT a permutation!"
    new = txt
    for pad, x, y, old, neu in PERM:
        # match: (label "OLD" \n\t\t(at X Y  -> capture so we only swap the text
        pat = re.compile(r'(\(label\s+")' + re.escape(old) +
                         r'("\s*\n\s*\(at\s+' + re.escape(fnum(x)) + r'\s+' + re.escape(fnum(y)) + r'\b)')
        hits = pat.findall(new)
        if len(hits) != 1:
            sys.exit(f"ABORT pad {pad}: expected exactly 1 label '{old}' at ({fnum(x)},{fnum(y)}), found {len(hits)}")
        new = pat.sub(r'\1' + neu.replace('\\', r'\\') + r'\2', new, count=1)
        print(f"  pad {pad:>3}: '{old}' -> '{neu}'")
    if new == txt:
        sys.exit("ABORT: no change made")
    sheet.write_text(new)
    print(f"wrote {sheet}  ({len(PERM)} labels permuted)")

if __name__ == "__main__":
    main()

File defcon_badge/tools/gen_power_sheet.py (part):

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            CustomPin("2", "PROG",     "output",         "L"),
            CustomPin("3", "GND",      "power_in",       "L"),
            CustomPin("4", "VCC",      "power_in",       "L"),
            CustomPin("5", "BAT",      "power_out",      "R"),
            CustomPin("6", "~{STDBY}", "open_collector", "R"),
            CustomPin("7", "~{CHRG}",  "open_collector", "R"),
            CustomPin("8", "CE",       "input",          "R"),
            CustomPin("9", "EP",       "power_in",       "L"),  # exposed thermal pad -> GND (ESOP-8)
        ],
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        sg.power_at_pin("J10", p, "GND", pwr_ref=f"#PWR_J10_{p}")
    sg.label_at_pin("J10", "A5", "CC1")
    sg.label_at_pin("J10", "B5", "CC2")
    sg.label_at_pin("J10", "A6", "USB_DP")
    sg.label_at_pin("J10", "B6", "USB_DP")
    sg.label_at_pin("J10", "A7", "USB_DM")
    sg.label_at_pin("J10", "B7", "USB_DM")
    # SBU1/SBU2 intentionally unconnected (no USB-C alt-mode used)
    sg.nc_at_pin("J10", "A8")
    sg.nc_at_pin("J10", "B8")
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
    # TP4056
    sg.power_at_pin("U10", "1", "GND", pwr_ref="#PWR_U10_T")
    sg.label_at_pin("U10", "2", "PROG_SET")
    sg.power_at_pin("U10", "3", "GND", pwr_ref="#PWR_U10_G")
    sg.label_at_pin("U10", "4", "VBUS")
    sg.label_at_pin("U10", "5", "BAT")
    sg.nc_at_pin("U10", "6")  # STDBY open-drain — leave floating
    sg.label_at_pin("U10", "7", "~{CHRG}")
    # CE → VBUS (charger input), NOT the switched +3V3 rail. Tying CE to the
    # post-switch LDO output disabled charging when the badge was off and made
    # a flat battery unable to bootstrap. VBUS keeps CE high whenever USB is
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    sg.label_at_pin("U10", "8", "VBUS")
    sg.power_at_pin("U10", "9", "GND", pwr_ref="#PWR_U10_EP")  # exposed thermal pad -> GND

    sg.label_at_pin("R12", "1", "PROG_SET")
    sg.power_at_pin("R12", "2", "GND", pwr_ref="#PWR_R12")

    sg.label_at_pin("R13", "1", "+3V3")
    sg.label_at_pin("R13", "2", "~{CHRG}")

    sg.label_at_pin("C21", "1", "BAT")
    sg.power_at_pin("C21", "2", "GND", pwr_ref="#PWR_C21")

    sg.label_at_pin("J11", "1", "BAT")
    sg.power_at_pin("J11", "2", "GND", pwr_ref="#PWR_J11")

    sg.label_at_pin("SW1", "2", "BAT")
    sg.label_at_pin("SW1", "1", "BAT_SW")
    sg.nc_at_pin("SW1", "3")  # second throw unused

    sg.label_at_pin("C22", "1", "BAT_SW")
    sg.power_at_pin("C22", "2", "GND", pwr_ref="#PWR_C22")

    sg.label_at_pin("U11", "1", "BAT_SW")
    sg.label_at_pin("U11", "3", "BAT_SW")
    sg.power_at_pin("U11", "2", "GND", pwr_ref="#PWR_U11")
    sg.label_at_pin("U11", "5", "+3V3")
    sg.nc_at_pin("U11", "4")  # NC pin on ME6211
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    sg.label_at_pin("C23", "1", "+3V3")
    sg.power_at_pin("C23", "2", "GND", pwr_ref="#PWR_C23")

    sg.label_at_pin("R14", "1", "BAT")
    sg.label_at_pin("R14", "2", "VBAT_SENSE")
    sg.label_at_pin("R15", "1", "VBAT_SENSE")
    sg.power_at_pin("R15", "2", "GND", pwr_ref="#PWR_R15")

    # PWR_FLAG for externally-sourced rails (VBUS from USB, BAT from cell)
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    sg.place("power:PWR_FLAG", "#FLG_GND", "PWR_FLAG", "", 210, 55,
             hide_value=True, desc="Declare GND as a power source (sinks-only net)")
    sg.power_at_pin("#FLG_GND", "1", "GND", pwr_ref="#PWR_FLGGND", stub=2.54)
    # (#FLG_BAT removed: BAT is already driven by the TP4056 BAT power-output pin;
    #  a PWR_FLAG on it shorted two power outputs -> pin_to_pin ERC error.)
    # BAT_SW is the switched-battery LDO input; flag as sourced (via SW1 from BAT)
    sg.place("power:PWR_FLAG", "#FLG_BSW", "PWR_FLAG", "", 240, 55,
             hide_value=True, desc="Declare BAT_SW as sourced (BAT through slide switch)")
    sg.label_at_pin("#FLG_BSW", "1", "BAT_SW", stub=2.54)

    # Cross-sheet hier_labels (boundary to top sheet).
    sg.add_hier("USB_DP",      290, 100, shape="bidirectional", rot=0)
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
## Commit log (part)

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2026-06-14 iter(22.1): STATE.md log catch-up
2026-06-14 chore: remove cleanup backup file
2026-06-14 chore: remove pass2 backup
2026-06-14 chore: drop arrange backup
2026-06-14 chore: drop floorplan/arrange backups
2026-06-14 chore: drop backups again
2026-06-15 chore: drop backups
2026-06-16 checking
2026-06-16 Audio realignment
2026-06-16 Placement changes
2026-06-16 Move buttons into an arc
2026-06-19 Routing redo
